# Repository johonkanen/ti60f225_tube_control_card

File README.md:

# ti60f225_tube_control_card

KiCad 10 migration of the tube control card with an Efinix Ti60F225 FPGA (channel switching, power scaling, bias control; Ethernet) of the tube amplifier, from Proteus. The schematic is redrawn from
the Proteus PDF and the PCB is rebuilt from the Gerber X2 export, so that every pad, track,
via and pour carries a net from the new schematic. The IPC-D-356A netlist of the CADCAM export
is the reference that every check compares against.

This is **rev A, the as-built baseline**. The redesign (ribbon cables, PCB-mount pots, the new
power section) starts from it. The amplifier project, its specification and the hardware state
are in [tube_amplifier_kicad](https://github.com/johonkanen/tube_amplifier_kicad). This card is not
installed in the amplifier, so the master repo does not include this repo as a submodule.

## Method

The shared [proteus2kicad](https://github.com/johonkanen/proteus2kicad) tools, a submodule in
`tools/p2k` (clone with `git clone --recurse-submodules`, or run `git submodule update --init`).
The phases and checks are in `tools/p2k/CONVERSION_PLAYBOOK.md`. Everything specific to this
board is in `p2k_config.py`.

## Status

Conversion plan: [PLAN.md](PLAN.md); progress: [STATUS.md](STATUS.md); prompt for the next agent session: [next_prompt.md](next_prompt.md).

Phase 0 (skeleton and inventory) and the Phase 1 preparation done: part map, symbol library
(U10 Ti60F225 as 8 units, pinout checked against Efinix), empty KiCad skeleton, netlist
comparison with decision D1 (split terminals drawn as one pin); `tools/check_all.sh` passes.
**Phase 1 (schematic) done**: all 12 sheets drawn by `tools/sheets/sheetNN.py` (146 of 146 parts, all
eight units of U10 with 62 no-connect flags); full netlist comparison against the IPC netlist: 0 missing
parts, 0 wrong-net pins, every net complete; ERC 0 errors, 14 explained warnings (single-pin nets);
decision D2 (no pin of type no_connect, ERC `no_connect_connected` fatal).
**Phase 2 (footprints) done**: `tools/gen_footprints.py` → `lib/footprint_map.csv` and
`lib/tube_control_card.pretty` (U10 = KiCad's TFBGA-225 P0.65 footprint unchanged, at 180 deg); all 146
parts fit their IPC pads within 0.030 mm (`p2k check_footprints --pcbnew`), pin order checked against the
unmoved KiCad footprints (`p2k check_pin_order`, `PIN_ORDER`). Results: ADC1 has VA / VIN swapped on the board
(finding 9 confirmed; fixed 2026-11-20 by hand edit H1); AP61202 pin 6 is PG, the sequencing is correct (finding 12 resolved); J11 is
numbered as a mirrored header like the HV board's J1, so the ribbon connects as drawn (finding 25; renumbered
to standard at both ends on 2026-11-20).
**Phase 3 (PCB) done**: `tools/make_pcb.sh` rebuilds
`kicad/tube_control_card.kicad_pcb` (4 layers, 1.6 mm, 3373 tracks, 240 vias, 20 zones, U10 BGA, SMD test
pads TP1-TP4) byte-identically; the Proteus copper is clean (0 shorts / 0 orphans / 0 opens besides the
five D1 split terminals), every pad / via / hole on its IPC position and net (`check_board`). Design rules
follow the measured Proteus copper (clearance 0.07 mm: 75 gaps under 0.1 mm on F.Cu, finding 26). Pad
decision (user, option A): the 15 parts whose KiCad pads reached Proteus tracks (TSSOP U1-U3 U5-U9 U11
U14, ADC1, U4, U12, headers J7 J11) have the Proteus pads; KiCad pads everywhere else. DRC: 0 shorts, 0
clearance, 0 mask bridges, 0 parity; only the accepted courtyard overlaps and the five D1 unconnected
items remain. `tools/check_all.sh`: ALL CHECKS PASSED.
**Phase 4 (independent verification) done** by a fresh session: KiCad's IPC-D-356 export matches the Proteus
netlist record for record (1132 / 1132; only the five D1 merges differ, accepted exactly), the gerber round
trip finds no copper difference on any of the 4 layers besides the decided KiCad pad shapes (pours
included; drills and the 2025 Excellon file 377 / 377), the only smaller drill is J8 (checked per pad), and
an independent reading of all 876 pins on the 12 PDF pages agrees with the IPC netlist and the KiCad
schematic (`tools/phase4_reading/`). 28 negative tests; finding 19 (level-shifter direction) resolved: no
problem. `tools/check_all.sh`: ALL CHECKS PASSED.
**Phase 5 (clean-up) done**, the user's choices: references placed clear of pads and silk by `p2k
place_refdes` (the last `make_pcb.sh` step; 13 dense passives get their reference on the Fab layer only);
dangling Proteus copper, the J1 body guess, the FLASH1 land pattern and all pad sizes / drills kept as built.
DRC warnings 370 → 83 (silk 326 → 39, none of them a reference); `tools/check_all.sh`: ALL CHECKS PASSED.
**The conversion is complete.** Rev A stays generated (`tools/make_pcb.sh`) until the user's first manual
layout change.
**Design fixes 2026-11-20** (user decisions; generators only, component values unchanged): AP61202 pin 6
renamed VOUT → PG (finding 12), the obsolete PDF sheet notes dropped (finding 6), the dangling Proteus
copper removed (finding 26: 26 draws `REMOVED_TRACKS` incl. the 56 mm GPIOL_N_18 stub, the lone GPIOL_N_10
via `REMOVED_VIAS`; 3347 tracks / 239 vias); DRC 83 → 71 violations, 0 dangling; `tools/check_all.sh`: ALL
CHECKS PASSED. Kept as built: findings 1, 13, 23, 24.
**Shared-tool migration 2026-11-20**: `tools/p2k` bumped to a9a286c and every board-local check wrapper
replaced by the shared proteus2kicad tools and `p2k_config.py` keys (`SPLIT_PIN_MERGES`, `SMD_FREE_PADS`,
`BGA_REFDES`, `PIN_ORDER`, `PHASE4_EXPECTED`, `DRILL_SMALLER` pad set, `ERC_FATAL_WARNINGS`, …); 14 board
tools deleted, generated files identical except the accepted report re-baselines; no strict-check opt-outs
Then **J11 renumbered to the standard 2x20 numbering** (finding 25, user decision, together with the HV
supplies J1 at the other end of the ribbon): `IPC_PIN_IDS` (old pin k → new k + 1 for odd k, k − 1 for even
k), the stock header footprint with its square pad on pin 1, copper unchanged (STATUS.md "Shared-tool
migration 2026-11-20"). `tools/check_all.sh`: ALL CHECKS PASSED.
**Generation stopped 2026-11-20** (user decision; last generated commit 827b0b7): the committed KiCad files
are the source now and are edited directly; the generators are frozen in `tools/generate/` (history, do not
run); `tools/check_all.sh` checks the committed files against the Proteus sources and the KiCad rules (no
regenerate / byte-compare steps).
**First hand edit (H1, 2026-11-20): finding 9 fixed** – ADC1 (ADC121C027) now has 3V3 on VA (pad A1 = SOT-23-6
pin 1) and the filtered BIASFEEDBACK node (R34 / C68) on VIN (pad COM2 = pin 3): the symbol's VA / VIN pins
exchanged in place with their datasheet pin types, on the board 5 F.Cu tracks moved, 5 removed and 8 added
around ADC1 (no via, no part moved); DRC unchanged (71 violations: 0 shorts, the accepted courtyards and D1
items). The checks accept exactly these two pin-net changes, the copper in a small area around ADC1 and the
+3 F.Cu track count (`tools/hand_edits.py`, STATUS.md "Hand edits after generation stopped"); ALL CHECKS PASSED.

Note: this Ti60F225 card is **not installed in the amplifier** (the Agilex 3 control card is). The
finished conversion is a reference and a starting point only.

v2.5, built 2025. `source/cadcam_rs274x/` is the earlier RS-274X export of the same version (cross-check only). v1 (built 2024, same outline and mounting holes) is not converted.

## Source

`fpga_boardv2.5.pdsprj` (Proteus 8.12). Exported 2026-11-19 from Proteus 8.12 SP2: schematic PDF, Gerber X2 CADCAM (metric)
with the IPC-D-356A netlist.

## Mechanical baseline

From the export (the fit reference for the redesign; the KiCad file is
`mechanical/tube_fpga_board_v2.5.kicad_pcb` in tube_amplifier_kicad):

```
outline: 97.79 x 55.88 mm, lower-left corner at (13.870, -42.750) in the Proteus frame
copper layers: 4; components: 146; mounting holes: 4
mounting holes (relative to the lower-left outline corner, mm):
  H1: x   93.130  y    3.750  drill 3.00 plated
  H2: x    4.130  y    3.750  drill 3.00 plated
  H3: x    4.130  y   51.750  drill 3.00 plated
  H4: x   93.130  y   51.750  drill 3.00 plated
```

## Layout

```
source/         Proteus exports (read-only)
  cadcam/         Gerber X2 export with the IPC-D-356A netlist (the reference)
  schematic_pdf/  schematic PDF to redraw from
  *.pdsprj        Proteus project (schematic values, devices, packages, pin names)
  cadcam_rs274x/  earlier RS-274X export (cross-check only)
reference/      tables derived from the IPC netlist (p2k ipc356; do not edit)
lib/            part_map.csv, tube_control_card.kicad_sym, footprints (generated until 2026-11-20, edited since)
kicad/          KiCad project: root sheet + one sheet per PDF page
tools/          board scripts: check_all.sh (every check, on the shared p2k tools), hand_edits.py (the recorded
                hand edits and the wrapper that accepts exactly them), test_no_connect.py, phase4_reading/
                (independent PDF transcript)
  generate/       FROZEN generators (generation stopped 2026-11-20; history, do not run): make_part_map.py,
                  gen_symbols.py, sheets/, gen_footprints.py, make_pcb.sh
tools/p2k/       proteus2kicad (submodule)
p2k_config.py   board configuration for the tools
```

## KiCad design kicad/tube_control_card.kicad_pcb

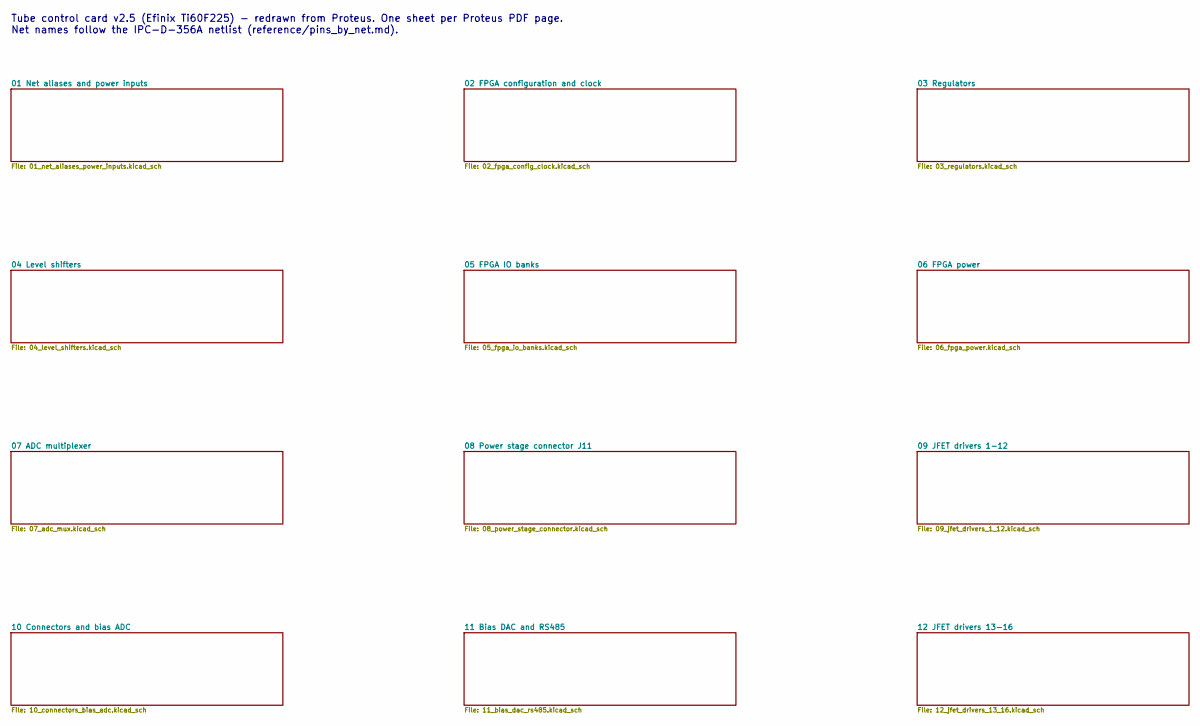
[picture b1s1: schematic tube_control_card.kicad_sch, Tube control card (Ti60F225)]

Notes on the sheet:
Tube control card v2.5 (Efinix Ti60F225) - redrawn from Proteus. One sheet per Proteus PDF page. Net names follow the IPC-D-356A netlist (reference/pins_by_net.md).

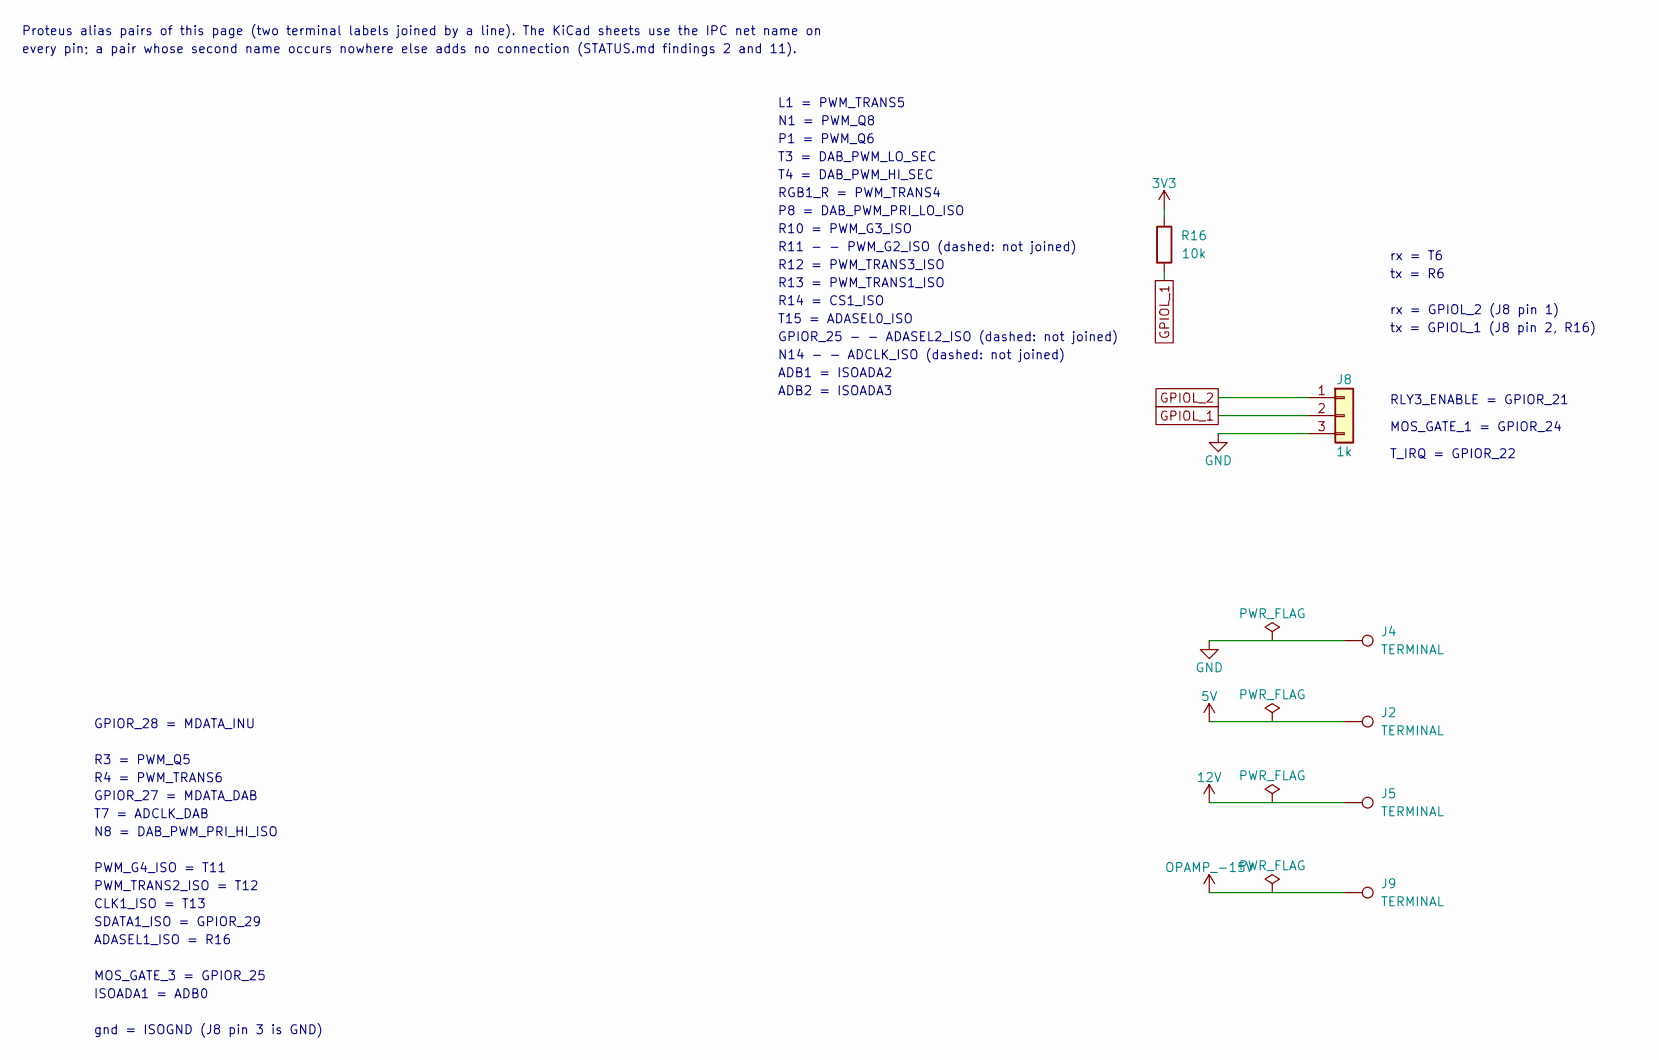
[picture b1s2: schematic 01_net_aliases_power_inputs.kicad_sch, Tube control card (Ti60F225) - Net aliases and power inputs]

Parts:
J2, J4, J5, J9: TERMINAL; Terminal_2x1_P5.00mm_D2.0mm_Drill1.4mm
J8: 1k; PinHeader_1x03_P2.54mm_Vertical
R16: 10k; R_0402_1005Metric

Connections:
3V3: R16.1; also elsewhere on the board
5V: J2.1; also elsewhere on the board
12V: J5.1; also elsewhere on the board
GND: J4.1, J8.3; also elsewhere on the board
GPIOL_1: J8.2, R16.2; also elsewhere on the board
GPIOL_2: J8.1; also elsewhere on the board
OPAMP_-15V: J9.1; also elsewhere on the board

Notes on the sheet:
Proteus alias pairs of this page (two terminal labels joined by a line). The KiCad sheets use the IPC net name on
every pin; a pair whose second name occurs nowhere else adds no connection (STATUS.md findings 2 and 11).
L1 = PWM_TRANS5
N1 = PWM_Q8
P1 = PWM_Q6
T3 = DAB_PWM_LO_SEC
T4 = DAB_PWM_HI_SEC
RGB1_R = PWM_TRANS4
P8 = DAB_PWM_PRI_LO_ISO
R10 = PWM_G3_ISO
R11 - - PWM_G2_ISO (dashed: not joined)
R12 = PWM_TRANS3_ISO
R13 = PWM_TRANS1_ISO
R14 = CS1_ISO
T15 = ADASEL0_ISO
GPIOR_25 - - ADASEL2_ISO (dashed: not joined)
N14 - - ADCLK_ISO (dashed: not joined)
ADB1 = ISOADA2
ADB2 = ISOADA3
GPIOR_28 = MDATA_INU
R3 = PWM_Q5
R4 = PWM_TRANS6
GPIOR_27 = MDATA_DAB
T7 = ADCLK_DAB
N8 = DAB_PWM_PRI_HI_ISO
PWM_G4_ISO = T11
PWM_TRANS2_ISO = T12
CLK1_ISO = T13
SDATA1_ISO = GPIOR_29
ADASEL1_ISO = R16
MOS_GATE_3 = GPIOR_25
ISOADA1 = ADB0
gnd = ISOGND (J8 pin 3 is GND)
rx = T6
tx = R6
rx = GPIOL_2 (J8 pin 1)
tx = GPIOL_1 (J8 pin 2, R16)
RLY3_ENABLE = GPIOR_21
MOS_GATE_1 = GPIOR_24
T_IRQ = GPIOR_22

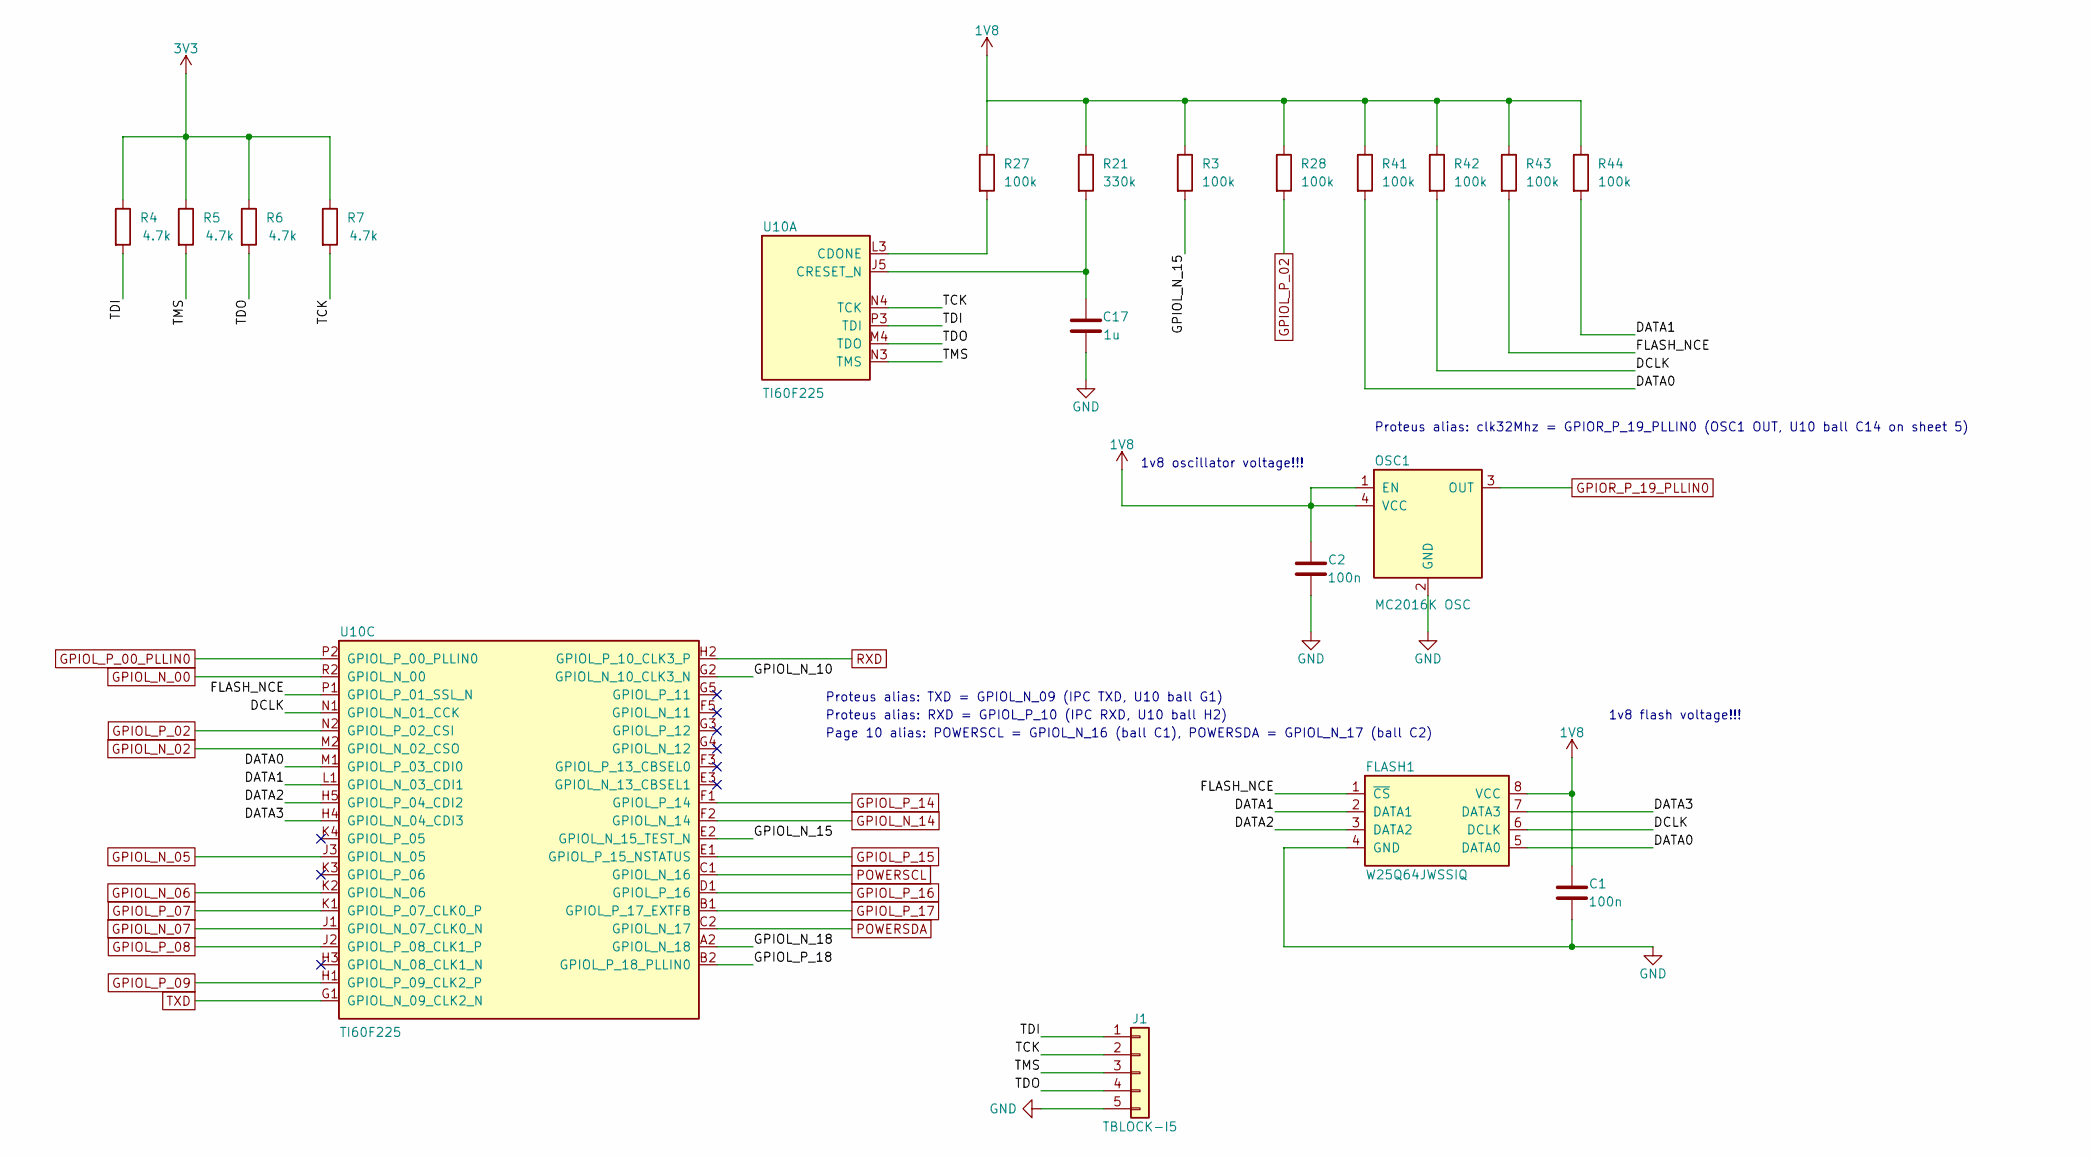
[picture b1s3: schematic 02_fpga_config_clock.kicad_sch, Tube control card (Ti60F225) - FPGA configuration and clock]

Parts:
C1, C2: 100n; C_0402_1005Metric
C17: 1u; C_0402_1005Metric
FLASH1: W25Q64JWSSIQ; SOIC-8_5.3x5.3mm_P1.27mm_Proteus
J1: TBLOCK-I5; TerminalBlock_Phoenix_MPT-0,5-5-2.54_1x05_P2.54mm_Horizontal
OSC1: MC2016K OSC; Oscillator_SMD_2.0x1.6mm_Proteus
R3, R27, R28, R41, R42, R43, R44: 100k; R_0402_1005Metric
R4, R5, R6, R7: 4.7k; R_0402_1005Metric
R21: 330k; R_0402_1005Metric
U10: TI60F225; TFBGA-225_10x10mm_Layout15x15_P0.65mm

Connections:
1V8: C1.2, C2.2, FLASH1.8 (VCC), OSC1.1 (EN), OSC1.4 (VCC), R3.1, R21.1, R27.1, R28.1, R41.1, R42.1, R43.1, R44.1; also elsewhere on the board
3V3: R4.1, R5.1, R6.1, R7.1; also elsewhere on the board
/02 FPGA configuration and clock/DATA0: FLASH1.5 (DATA0), R41.2, U10.M1 (GPIOL_P_03_CDI0)
/02 FPGA configuration and clock/DATA1: FLASH1.2 (DATA1), R44.2, U10.L1 (GPIOL_N_03_CDI1)
/02 FPGA configuration and clock/DATA2: FLASH1.3 (DATA2), U10.H5 (GPIOL_P_04_CDI2)
/02 FPGA configuration and clock/DATA3: FLASH1.7 (DATA3), U10.H4 (GPIOL_N_04_CDI3)
/02 FPGA configuration and clock/DCLK: FLASH1.6 (DCLK), R42.2, U10.N1 (GPIOL_N_01_CCK)
/02 FPGA configuration and clock/FLASH_NCE: FLASH1.1 (~CS), R43.2, U10.P1 (GPIOL_P_01_SSL_N)
/02 FPGA configuration and clock/GPIOL_N_10: U10.G2 (GPIOL_N_10_CLK3_N)
/02 FPGA configuration and clock/GPIOL_N_15: R3.2, U10.E2 (GPIOL_N_15_TEST_N)
/02 FPGA configuration and clock/GPIOL_N_18: U10.A2 (GPIOL_N_18)
/02 FPGA configuration and clock/GPIOL_P_18: U10.B2 (GPIOL_P_18_PLLIN0)
/02 FPGA configuration and clock/TCK: J1.2, R7.2, U10.N4 (TCK)
/02 FPGA configuration and clock/TDI: J1.1, R4.2, U10.P3 (TDI)
/02 FPGA configuration and clock/TDO: J1.4, R6.2, U10.M4 (TDO)
/02 FPGA configuration and clock/TMS: J1.3, R5.2, U10.N3 (TMS)
GND: C1.1, C2.1, C17.1, FLASH1.4 (GND), J1.5, OSC1.2 (GND); also elsewhere on the board
GPIOL_N_00: U10.R2 (GPIOL_N_00); also elsewhere on the board
GPIOL_N_02: U10.M2 (GPIOL_N_02_CSO); also elsewhere on the board
GPIOL_N_05: U10.J3 (GPIOL_N_05); also elsewhere on the board
GPIOL_N_06: U10.K2 (GPIOL_N_06); also elsewhere on the board
GPIOL_N_07: U10.J1 (GPIOL_N_07_CLK0_N); also elsewhere on the board
GPIOL_N_14: U10.F2 (GPIOL_N_14); also elsewhere on the board
GPIOL_P_00_PLLIN0: U10.P2 (GPIOL_P_00_PLLIN0); also elsewhere on the board
GPIOL_P_02: R28.2, U10.N2 (GPIOL_P_02_CSI); also elsewhere on the board
GPIOL_P_07: U10.K1 (GPIOL_P_07_CLK0_P); also elsewhere on the board
GPIOL_P_08: U10.J2 (GPIOL_P_08_CLK1_P); also elsewhere on the board
GPIOL_P_09: U10.H1 (GPIOL_P_09_CLK2_P); also elsewhere on the board
GPIOL_P_14: U10.F1 (GPIOL_P_14); also elsewhere on the board
GPIOL_P_15: U10.E1 (GPIOL_P_15_NSTATUS); also elsewhere on the board
GPIOL_P_16: U10.D1 (GPIOL_P_16); also elsewhere on the board
GPIOL_P_17: U10.B1 (GPIOL_P_17_EXTFB); also elsewhere on the board
GPIOR_P_19_PLLIN0: OSC1.3 (OUT); also elsewhere on the board
unnamed: R27.2, U10.L3 (CDONE)
unnamed: C17.2, R21.2, U10.J5 (CRESET_N)
POWERSCL: U10.C1 (GPIOL_N_16); also elsewhere on the board
POWERSDA: U10.C2 (GPIOL_N_17); also elsewhere on the board
RXD: U10.H2 (GPIOL_P_10_CLK3_P); also elsewhere on the board
TXD: U10.G1 (GPIOL_N_09_CLK2_N); also elsewhere on the board

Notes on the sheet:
1v8 oscillator voltage!!!
Proteus alias: clk32Mhz = GPIOR_P_19_PLLIN0 (OSC1 OUT, U10 ball C14 on sheet 5)
Proteus alias: TXD = GPIOL_N_09 (IPC TXD, U10 ball G1)
Proteus alias: RXD = GPIOL_P_10 (IPC RXD, U10 ball H2)
Page 10 alias: POWERSCL = GPIOL_N_16 (ball C1), POWERSDA = GPIOL_N_17 (ball C2)
1v8 flash voltage!!!

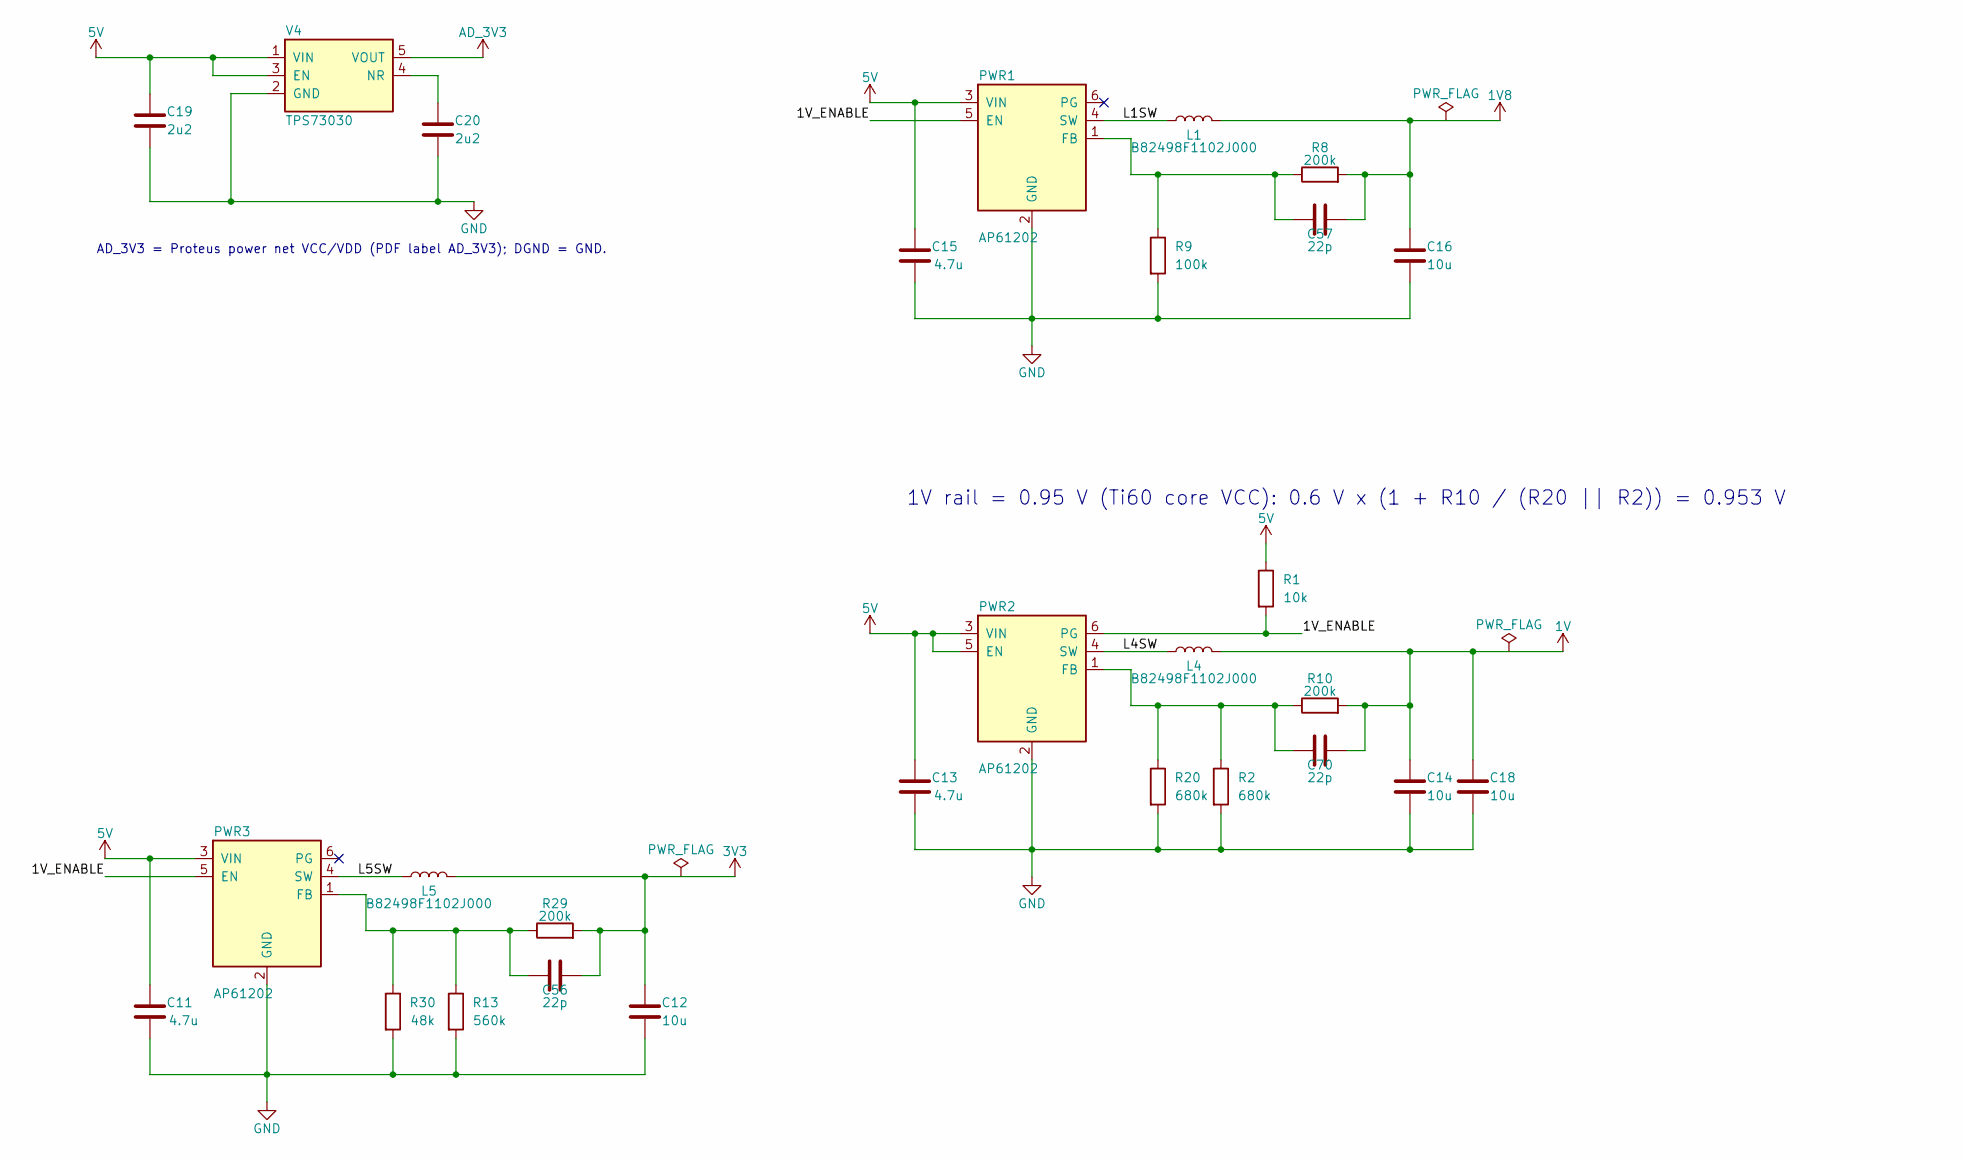
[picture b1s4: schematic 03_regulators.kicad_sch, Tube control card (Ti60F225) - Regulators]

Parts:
C11, C13, C15: 4.7u; C_0402_1005Metric
C12, C14, C16, C18: 10u; C_0402_1005Metric
C19, C20: 2u2; C_0603_1608Metric
C56, C57, C70: 22p; C_0402_1005Metric
L1, L4, L5: B82498F1102J000; L_0805_2012Metric
PWR1, PWR2, PWR3: AP61202; SOT-563_Proteus
R1: 10k; R_0402_1005Metric
R2, R20: 680k; R_0402_1005Metric
R8, R10, R29: 200k; R_0402_1005Metric
R9: 100k; R_0402_1005Metric
R13: 560k; R_0402_1005Metric
R30: 48k; R_0402_1005Metric
V4: TPS73030; SOT-23-5_Proteus

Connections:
1V: C14.2, C18.2, C70.2, L4.2, R10.2; also elsewhere on the board
1V8: C16.2, C57.2, L1.2, R8.2; also elsewhere on the board
3V3: C12.2, C56.2, L5.2, R29.2; also elsewhere on the board
5V: C11.2, C13.2, C15.2, C19.1, PWR1.3 (VIN), PWR2.3 (VIN), PWR2.5 (EN), PWR3.3 (VIN), R1.1, V4.1 (VIN), V4.3 (EN); also elsewhere on the board
/03 Regulators/1V_ENABLE: PWR1.5 (EN), PWR2.6 (PG), PWR3.5 (EN), R1.2
/03 Regulators/L1SW: L1.1, PWR1.4 (SW)
/03 Regulators/L4SW: L4.1, PWR2.4 (SW)
/03 Regulators/L5SW: L5.1, PWR3.4 (SW)
AD_3V3: V4.5 (VOUT); also elsewhere on the board
GND: C11.1, C12.1, C13.1, C14.1, C15.1, C16.1, C18.1, C19.2, C20.2, PWR1.2 (GND), PWR2.2 (GND), PWR3.2 (GND), R2.2, R9.2, R13.2, R20.2, R30.2, V4.2 (GND); also elsewhere on the board
unnamed: C57.1, PWR1.1 (FB), R8.1, R9.1
unnamed: C70.1, PWR2.1 (FB), R2.1, R10.1, R20.1
unnamed: C56.1, PWR3.1 (FB), R13.1, R29.1, R30.1
unnamed: C20.1, V4.4 (NR)

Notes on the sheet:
1V rail = 0.95 V (Ti60 core VCC): 0.6 V x (1 + R10 / (R20 || R2)) = 0.953 V
AD_3V3 = Proteus power net VCC/VDD (PDF label AD_3V3); DGND = GND.

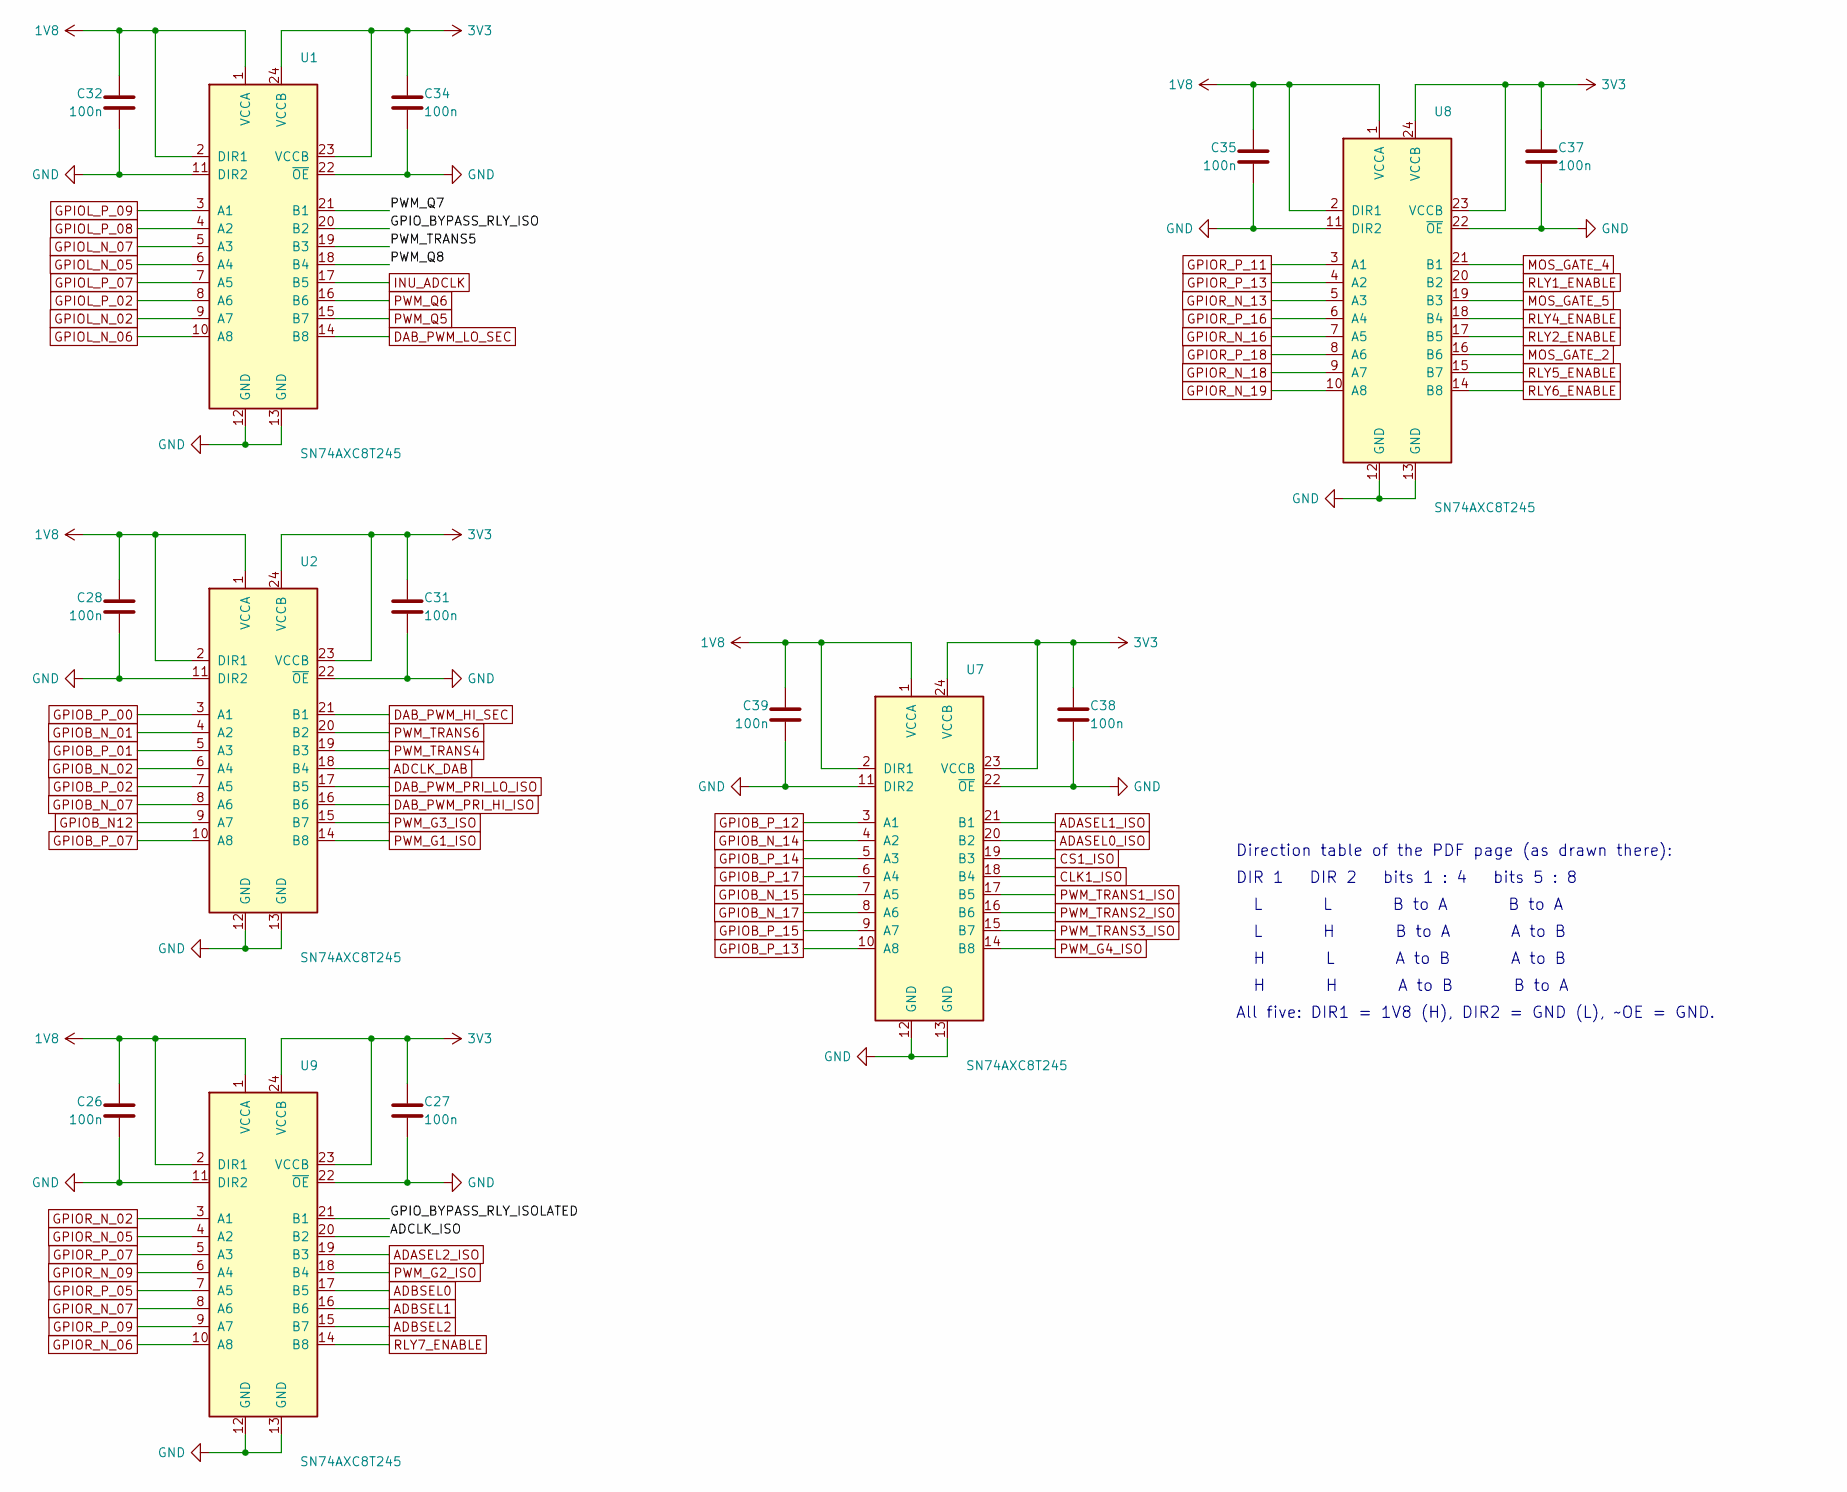
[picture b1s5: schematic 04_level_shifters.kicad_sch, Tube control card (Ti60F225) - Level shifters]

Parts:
C26, C27, C28, C31, C32, C34, C35, C37, C38, C39: 100n; C_0402_1005Metric
U1, U2, U7, U8, U9: SN74AXC8T245; TSSOP-24_4.4x7.8mm_P0.65mm_ProteusPads

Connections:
1V8: C26.2, C28.2, C32.2, C35.2, C39.2, U1.1 (VCCA), U1.2 (DIR1), U2.1 (VCCA), U2.2 (DIR1), U7.1 (VCCA), U7.2 (DIR1), U8.1 (VCCA), U8.2 (DIR1), U9.1 (VCCA), U9.2 (DIR1); also elsewhere on the board
3V3: C27.2, C31.2, C34.2, C37.2, C38.2, U1.23 (VCCB), U1.24 (VCCB), U2.23 (VCCB), U2.24 (VCCB), U7.23 (VCCB), U7.24 (VCCB), U8.23 (VCCB), U8.24 (VCCB), U9.23 (VCCB), U9.24 (VCCB); also elsewhere on the board
/04 Level shifters/ADCLK_ISO: U9.20 (B2)
/04 Level shifters/GPIO_BYPASS_RLY_ISO: U1.20 (B2)
/04 Level shifters/GPIO_BYPASS_RLY_ISOLATED: U9.21 (B1)
/04 Level shifters/PWM_Q7: U1.21 (B1)
/04 Level shifters/PWM_Q8: U1.18 (B4)
/04 Level shifters/PWM_TRANS5: U1.19 (B3)
ADASEL0_ISO: U7.20 (B2); also elsewhere on the board
ADASEL1_ISO: U7.21 (B1); also elsewhere on the board
ADASEL2_ISO: U9.19 (B3); also elsewhere on the board
ADBSEL0: U9.17 (B5); also elsewhere on the board
ADBSEL1: U9.16 (B6); also elsewhere on the board
ADBSEL2: U9.15 (B7); also elsewhere on the board
ADCLK_DAB: U2.18 (B4); also elsewhere on the board
CLK1_ISO: U7.18 (B4); also elsewhere on the board
CS1_ISO: U7.19 (B3); also elsewhere on the board
DAB_PWM_HI_SEC: U2.21 (B1); also elsewhere on the board
DAB_PWM_LO_SEC: U1.14 (B8); also elsewhere on the board
DAB_PWM_PRI_HI_ISO: U2.16 (B6); also elsewhere on the board
DAB_PWM_PRI_LO_ISO: U2.17 (B5); also elsewhere on the board
GND: C26.1, C27.1, C28.1, C31.1, C32.1, C34.1, C35.1, C37.1, C38.1, C39.1, U1.11 (DIR2), U1.12 (GND), U1.13 (GND), U1.22 (~OE), U2.11 (DIR2), U2.12 (GND), U2.13 (GND), U2.22 (~OE), U7.11 (DIR2), U7.12 (GND), U7.13 (GND), U7.22 (~OE), U8.11 (DIR2), U8.12 (GND), U8.13 (GND), U8.22 (~OE), U9.11 (DIR2), U9.12 (GND), U9.13 (GND), U9.22 (~OE); also elsewhere on the board
GPIOB_N12: U2.9 (A7); also elsewhere on the board
GPIOB_N_01: U2.4 (A2); also elsewhere on the board
GPIOB_N_02: U2.6 (A4); also elsewhere on the board
GPIOB_N_07: U2.8 (A6); also elsewhere on the board
GPIOB_N_14: U7.4 (A2); also elsewhere on the board
GPIOB_N_15: U7.7 (A5); also elsewhere on the board
GPIOB_N_17: U7.8 (A6); also elsewhere on the board
GPIOB_P_00: U2.3 (A1); also elsewhere on the board
GPIOB_P_01: U2.5 (A3); also elsewhere on the board
GPIOB_P_02: U2.7 (A5); also elsewhere on the board
GPIOB_P_07: U2.10 (A8); also elsewhere on the board
GPIOB_P_12: U7.3 (A1); also elsewhere on the board
GPIOB_P_13: U7.10 (A8); also elsewhere on the board
GPIOB_P_14: U7.5 (A3); also elsewhere on the board
GPIOB_P_15: U7.9 (A7); also elsewhere on the board
GPIOB_P_17: U7.6 (A4); also elsewhere on the board
GPIOL_N_02: U1.9 (A7); also elsewhere on the board
GPIOL_N_05: U1.6 (A4); also elsewhere on the board
GPIOL_N_06: U1.10 (A8); also elsewhere on the board
GPIOL_N_07: U1.5 (A3); also elsewhere on the board
GPIOL_P_02: U1.8 (A6); also elsewhere on the board
GPIOL_P_07: U1.7 (A5); also elsewhere on the board
GPIOL_P_08: U1.4 (A2); also elsewhere on the board
GPIOL_P_09: U1.3 (A1); also elsewhere on the board
GPIOR_N_02: U9.3 (A1); also elsewhere on the board
GPIOR_N_05: U9.4 (A2); also elsewhere on the board
GPIOR_N_06: U9.10 (A8); also elsewhere on the board
GPIOR_N_07: U9.8 (A6); also elsewhere on the board
GPIOR_N_09: U9.6 (A4); also elsewhere on the board
GPIOR_N_13: U8.5 (A3); also elsewhere on the board
GPIOR_N_16: U8.7 (A5); also elsewhere on the board
GPIOR_N_18: U8.9 (A7); also elsewhere on the board
GPIOR_N_19: U8.10 (A8); also elsewhere on the board
GPIOR_P_05: U9.7 (A5); also elsewhere on the board
GPIOR_P_07: U9.5 (A3); also elsewhere on the board
GPIOR_P_09: U9.9 (A7); also elsewhere on the board
GPIOR_P_11: U8.3 (A1); also elsewhere on the board
GPIOR_P_13: U8.4 (A2); also elsewhere on the board
GPIOR_P_16: U8.6 (A4); also elsewhere on the board
GPIOR_P_18: U8.8 (A6); also elsewhere on the board
INU_ADCLK: U1.17 (B5); also elsewhere on the board
MOS_GATE_2: U8.16 (B6); also elsewhere on the board
MOS_GATE_4: U8.21 (B1); also elsewhere on the board
MOS_GATE_5: U8.19 (B3); also elsewhere on the board
PWM_G1_ISO: U2.14 (B8); also elsewhere on the board
PWM_G2_ISO: U9.18 (B4); also elsewhere on the board
PWM_G3_ISO: U2.15 (B7); also elsewhere on the board
PWM_G4_ISO: U7.14 (B8); also elsewhere on the board
PWM_Q5: U1.15 (B7); also elsewhere on the board
PWM_Q6: U1.16 (B6); also elsewhere on the board
PWM_TRANS1_ISO: U7.17 (B5); also elsewhere on the board
PWM_TRANS2_ISO: U7.16 (B6); also elsewhere on the board
PWM_TRANS3_ISO: U7.15 (B7); also elsewhere on the board
PWM_TRANS4: U2.19 (B3); also elsewhere on the board
PWM_TRANS6: U2.20 (B2); also elsewhere on the board
RLY1_ENABLE: U8.20 (B2); also elsewhere on the board
RLY2_ENABLE: U8.17 (B5); also elsewhere on the board
RLY4_ENABLE: U8.18 (B4); also elsewhere on the board
RLY5_ENABLE: U8.15 (B7); also elsewhere on the board
RLY6_ENABLE: U8.14 (B8); also elsewhere on the board
RLY7_ENABLE: U9.14 (B8); also elsewhere on the board

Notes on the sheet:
Direction table of the PDF page (as drawn there):
DIR 1 DIR 2 bits 1 : 4 bits 5 : 8
L L B to A B to A
L H B to A A to B
H L A to B A to B
H H A to B B to A
All five: DIR1 = 1V8 (H), DIR2 = GND (L), ~OE = GND.
